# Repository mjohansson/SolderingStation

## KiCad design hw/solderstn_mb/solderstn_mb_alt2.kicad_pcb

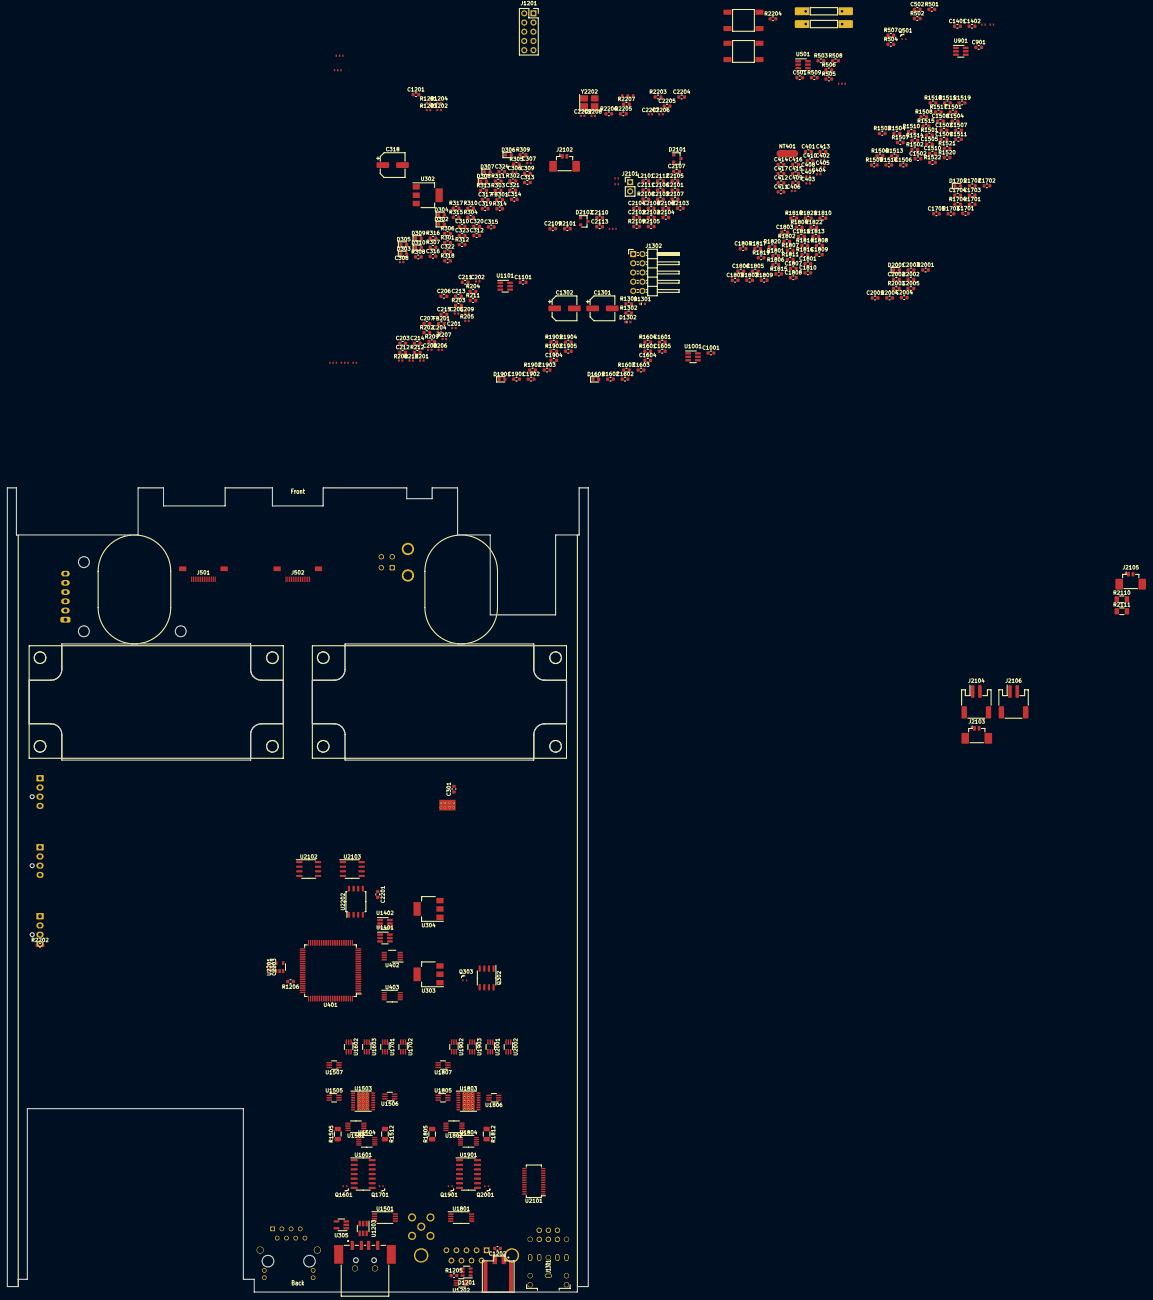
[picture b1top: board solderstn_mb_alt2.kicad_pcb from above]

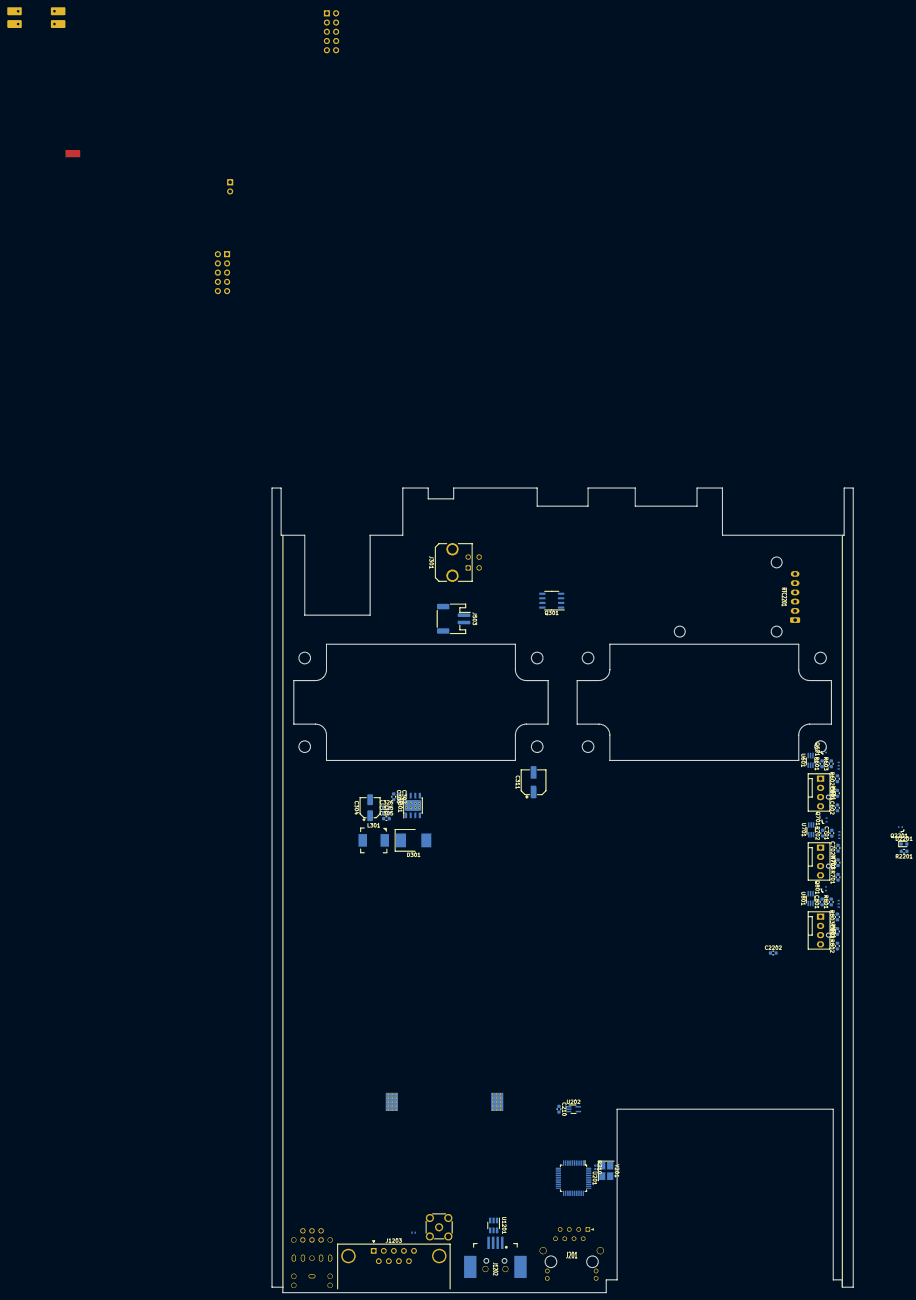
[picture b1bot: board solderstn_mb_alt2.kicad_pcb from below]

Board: 4 copper layers, 160.0 x 221.5 mm, 411 parts (56 on the bottom side), 267 nets, no tracks yet.

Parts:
C201, C202, C204, C205: DNP; C_0402_1005Metric
C203, C206, C207, C210, C211, C213, C215, C301, C309, C317, C321, C411, C416, C417, C501, C502, C602, C702, C802, C901, C1001, C1101, C1201, C1202, C1401, C1402, C1509, C1510, C1511, C1601, C1603, C1604, C1605, C1701, C1703, C1704, C1705, C1809, C1810, C1811, C1901, C1903, C1904, C1905, C2001, C2003, C2004, C2005, C2101, C2107, C2111, C2201, C2202, C2203, C2204, C2205: 100n; C_0603_1608Metric
C208, C209: 27p; C_0402_1005Metric
C212, C214, C302, C303, C305, C312, C313, C319, C320, C322, C323, C324, C325, C326, C401: 10u; C_0603_1608Metric
C304: APXG160ARA101ME61G; CP_Elec_5x5.8
C306: 15n; C_0402_1005Metric
C307: 10pF; C_0402_1005Metric
C308: 3n9; C_0402_1005Metric
C310, C314, C315, C601, C701, C801: 10u/16V; C_0603_1608Metric
C311, C318: UCL1V470MCL1GS; CP_Elec_6.3x5.8
C316, C412, C413, C415, C1508, C1808: 1u; C_0603_1608Metric
C402, C403, C404, C405, C406, C407, C408: 100n; C_0402_1005Metric
C409, C410, C2106, C2109, C2110, C2113: 2u2; C_0603_1608Metric
C414: 22u; C_0603_1608Metric
C1301, C1302: 47u/10V; CP_Elec_6.3x5.8
C1501, C1505, C1507, C1801, C1805, C1807: 10n; C_0603_1608Metric
C1502, C1802: 4n7; C_0603_1608Metric
C1503, C1504, C1506, C1803, C1804, C1806: 220n; C_0603_1608Metric
C1602, C1702, C1902, C2002: 1u/10V; C_0603_1608Metric
C2102: 22n; C_0603_1608Metric
C2103: 4p7; C_0603_1608Metric
C2104, C2108, C2112: 470n; C_0603_1608Metric
C2105: 1n; C_0603_1608Metric
C2206, C2207, C2208, C2209: 10p; C_0402_1005Metric
D301: MBRS340T3G; MBRS3xx_SMC_CASE_403AC
D302: Yellow; LED_0603_1608Metric
D303, D304, D305, D306, D307, D308, D309: Green; LED_0603_1608Metric
D310, D1601, D1701, D1901, D2001: Red; LED_0603_1608Metric
D1201: SP0505BAHT; SOT-23-6
D1301, D1302: SLESD5Z5V; D_SOD-523
D2101, D2102: CM1213A-01SO; SOT-23
D2201: LED_gr; LED_0603_1608Metric
FB201, FB301: 60R@100M; L_0603_1608Metric
J201: 74980104400; 74980104400_WE-RJ45_LAN_trx
J301: Molex_MicroFit_30-43045-0421; Molex_Micro-Fit_3.0_43045-0421_2x02-1MP_P3.00mm_Horizontal
J501, J502: FFC_conn_14p; FPC_14p_05mm-Molex_5052781433
J503: JST_S2B-PH-SM4-TB; JST_PH_S2B-PH-SM4-TB_1x02-1MP_P2.00mm_Horizontal
J1201: Conn_02x05_Odd_Even; PinSocket_2x05_P2.54mm_Vertical
J1202: USB_B-TE_1734346-1; TE_1734346
J1203: DB9_Male_MountingHoles; DSub9-Kycon_K22X-EP9P-N
J1204: USB_A-CUI-UJ2-AH-1-SMT; CUI-UJ2_AH_1_SMT
J1205: Molex_NanoFit-1x02; Molex_NanoFit_105430-1102_1x02_P2.50mm_Horizontal
J1301: SJ-3571N
J1302: Conn_02x05_Odd_Even; PinHeader_2x05_P2.54mm_Horizontal
J2101: Conn_01x02; PinHeader_1x02_P2.54mm_Vertical
J2102: Molex_PicoBlade-53398-0271; Molex_PicoBlade_53398-0271_1x02-1MP_P1.25mm_Vertical
J2103, J2105: CES-30207-158L120-67_Molex-PicoBlade_conn; Molex_PicoBlade_53398-0271_1x02-1MP_P1.25mm_Vertical
J2104, J2106: CES-703116-28PM_JST-conn; JST_PH_S2B-PH-SM4-TB_1x02-1MP_P2.00mm_Horizontal
J2107: Conn_Coaxial; SMA_Molex_73251-2200_Horizontal
JP201, JP1401, JP1402, JP2102, JP2103, JP2106: dogbone_2_ud; db2_ud_0402
JP202, JP203, JP501, JP601, JP701, JP801, JP2101, JP2104, JP2105: dogbone_3_ud; db3_ud_0402
JP2201: dogbone_3_ud; db3_ud_0603
L301: ASPI-0630LR-3R3M-T15; ASPI-0603LR
L2101: 56nH(LQW18AN56NJ00D); L_0603_1608Metric
LS2101, LS2103: CES-30207-158L120-67; CUI_CES-30207
LS2102, LS2104: CES-703116-28PM; CUI_CES-703116-28PM
M501, M502: FFC_retention_clamp; FFC_retention_clamp_14pin_7_5mm
M601, M701, M801: Fan_4pin; FanPinHeader_1x04_P2.54mm_Vertical
NT401: Net-Tie_2; NetTie-2_SMD_Pad2.0mm
Q301, Q302: Si4497DY; SOIC-8_3.9x4.9mm_P1.27mm
Q303, Q501, Q601, Q701, Q801, Q2201: DMG1012T; SOT-523
Q1601, Q1701, Q1901, Q2001: DMG1013T; SOT-523
R201, R205, R206, R207, R208: 5k1; R_0402_1005Metric
R202, R203: 330; R_0603_1608Metric
R204, R211, R212, R302, R304, R307, R308, R309, R502, R509, R602, R603, R702, R703, R802, R803, R1503, R1508, R1509, R1510, R1518, R1519, R1520, R1521, R1522, R1603, R1703, R1803, R1808, R1809, R1810, R1818, R1819, R1820, R1821, R1822, R1903, R2003, R2106, R2109, R2203, R2206: 10k; R_0603_1608Metric
R209, R508, R2207: 0R; R_0603_1608Metric
R210: 0R; R_0402_1005Metric
R213: 6.19k; R_0402_1005Metric
R301: 390k; R_0603_1608Metric
R303: 68k; R_0603_1608Metric
R305: 1k8; R_0603_1608Metric
R306, R312, R313, R314, R1501, R1502, R1504, R1506, R1511, R1514, R1516, R1604, R1704, R1801, R1802, R1804, R1806, R1811, R1814, R1816, R1904, R2004, R2102, R2103, R2201, R2202: 1k; R_0603_1608Metric
R310, R311, R2204, R2205: 4k7; R_0603_1608Metric
R315, R316, R317: 100R; R_0603_1608Metric
R318: 470R; R_0603_1608Metric
R501, R503, R506: 20k; R_0603_1608Metric
R504, R505: 160k; R_0603_1608Metric
R507: 27k; R_0603_1608Metric
R601, R701, R801: 12k; R_0603_1608Metric
R1201, R1202, R1203, R1204: 1k; R_0402_1005Metric
R1205, R1206, R1301, R1302: 100; R_0603_1608Metric
R1505, R1512, R1805, R1812: 10mR; R_1206_3216Metric
R1507, R1517, R1807, R1817: 330k; R_0603_1608Metric
R1513, R1515, R1813, R1815: 5k6; R_0603_1608Metric
R1601, R1602, R1701, R1702, R1901, R1902, R2001, R2002, R2104, R2107: 15k; R_0603_1608Metric
R2101: 560; R_0603_1608Metric
R2105, R2108: 2k2; R_0603_1608Metric
R2110, R2111: 0R; R_1206_3216Metric
RTC2201: DS3231_Module_6pins; DS3231_module_6pin_horizontal_mnt
SW2201, SW2202: Pushbutton_SMD_TS-1102W-4316; SMD_PUSHBTN_6x6mm
U201: IP101GA; LQFP-48_7x7mm_P0.5mm
U202: 74LVC1G126SE; SOT-353_SC-70-5_Handsoldering
U301: TPS54332DDA; TI_SO-PowerPAD-8_ThermalVias
U302, U303, U304: TLV1117LV30DCY; SOT-223-3_TabPin2
U305: AP22811AW5; SOT-23-5_HandSoldering
U401: STM32F429VITx; LQFP-100_14x14mm_P0.5mm
U402: REF6125IDGK; VSSOP-8_3.0x3.0mm_P0.65mm
U403: TLV9052SIDGS; VSSOP-10_3x3mm_P0.5mm
U501: TLV9051SIDBV; SOT-23-6_Handsoldering
U601, U701, U801, U1202: 74LVC2G17gw; SOT-363_SC-70-6_Handsoldering
U901, U1001, U1101: TMP100; SOT-23-6_Handsoldering
U1201, U1203: USBLC6-2SC6; SOT-23-6_Handsoldering
U1401, U1402: TMUX1219; SOT-23-6_Handsoldering
U1501, U1801: AD8552ARU; TSSOP-8_4.4x3mm_P0.65mm
U1502, U1504, U1802, U1804: INA226; VSSOP-10_3x3mm_P0.5mm
U1503, U1803: TPS2HB16AQ1; HTSSOP-16-1EP_4.4x5mm_P0.65mm_EP3.4x5mm_Mask3x3mm_ThermalVi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
U1505, U1506, U1507, U1603, U1702, U1805, U1806, U1807, U1903, U2002: 74LVC1G11dck; SOT-363_SC-70-6_Handsoldering
U1601, U1901: NE556d; SOIC-14_3.9x8.7mm_P1.27mm
U1602, U1701, U1902, U2001: 74LVC1G175dck; SOT-363_SC-70-6_Handsoldering
U2101: Si4735-D60-GU; SSOP-24_3.9x8.7mm_P0.635mm
U2102, U2103: TS4990IDT; SOIC-8_3.9x4.9mm_P1.27mm
U2201: MCP1316T-26LE-OT; SOT-23-5
U2202: W25Q64FV; SOIC-8_5.275x5.275mm_P1.27mm
Y201: TSX-3225 25.0000MF10P-C; Crystal_SMD_SeikoEpson_TSX3225-4Pin_3.2x2.5mm_HandSoldering
Y2202: TSX-3225 16.0000MF18X-AC3; Crystal_SMD_SeikoEpson_TSX3225-4Pin_3.2x2.5mm_HandSoldering

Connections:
+12V: C315.1, C1502.2, C1503.2, C1802.2, C1803.2, Q302.5, Q302.6, Q302.7, Q302.8, R311.1, R1513.1, R1515.2, R1813.1, R1815.2, U1502.8, U1503.17, U1504.8, U1802.8, U1803.17, U1804.8
+VDC: J301.2, J301.3, Q301.5, Q301.6, Q301.7, Q301.8
/Audio & FM-radio/Audio_L_int: J1201.2, R2111.1
/Audio & FM-radio/Audio_R_int: J1201.6, R2110.1
/Audio & FM-radio/FMI: C2105.1, D2102.1, J2102.1, JP2106.1
/Ethernet/50M_CLKO: U201.16, U202.2
/Ethernet/LED0_LINK: J201.11, R208.2, U201.9
/Ethernet/LED1_DUPLEX: R207.2, U201.10
/Ethernet/LED2_10M_LINK_ACT: J201.10, JP201.1, JP201.2, R206.2, U201.12
/Ethernet/LED3_100M_LINK_ACT: R202.2, R205.2, U201.13
/Ethernet/RMII: R211.1, U201.1
/Ethernet/RXN: C205.1, J201.6, U201.30
/Ethernet/RXP: C204.1, J201.3, U201.31
/Ethernet/TXN: C202.1, J201.2, U201.33
/Ethernet/TXP: C201.1, J201.1, U201.34
/Rear panel connections/Audio_L: J1201.1, U2103.8
/Rear panel connections/Audio_R: J1201.5, U2102.8
/Rear panel connections/CH_A_HEATER_1: R1505.1, R1601.1, U1502.10
/Rear panel connections/CH_A_HEATER_2: R1512.1, R1701.1, U1504.10
/Rear panel connections/CH_A_TC1: R1501.2, R1502.2, R1504.1
/Rear panel connections/CH_B_HEATER_1: R1805.1, R1901.1, U1802.10
/Rear panel connections/CH_B_HEATER_2: R1812.1, R2001.1, U1804.10
/Rear panel connections/CH_B_TC1: R1801.2, R1802.2, R1804.1
/Rear panel connections/Headphone connector asm/Audio_L_ch: J1301.8, J1302.1, R1202.2
/Rear panel connections/Headphone connector asm/Audio_R_ch: J1301.5, J1302.5, R1201.2
/Rear panel connections/Headphone connector asm/Audio_int_L: J1301.7, J1302.2, R1203.2
/Rear panel connections/Headphone connector asm/Audio_int_R: J1301.4, J1302.6, R1204.2
/Rear panel connections/Headphone connector asm/L_ch_out: D1301.1, J1301.2, R1302.1
/Rear panel connections/Headphone connector asm/R_ch_out: D1302.1, J1301.3, R1301.1
/STM32F429 MCU/32kHz: JP2201.1, R2202.1, RTC2201.1
/STM32F429 MCU/AUX_HOST_RX: J502.8, U401.97
/STM32F429 MCU/AUX_HOST_TX: J502.9, U401.98
/STM32F429 MCU/CH_A_KTY_REED_BIAS_EN: U401.61, U403.5
/STM32F429 MCU/CH_B_KTY_REED_BIAS_EN: U401.62, U403.6
/STM32F429 MCU/DLED_WDT: Q2201.1, U401.7, U2201.4
/STM32F429 MCU/Flash_MISO: U401.44, U2202.2
/STM32F429 MCU/~Flash_CSn~: U401.41, U2202.1
/STM32F429 MCU/~RTC_INTn~: RTC2201.2, U401.47
/STM32F429 PWR/Vref_2v5: C414.1, C415.1, C416.1, U401.21, U402.5, U402.6, U403.3, U403.7
/Weller contol/CH_A_KTY_REED_BIAS: R1501.1, R1511.1, U403.1, U403.2
/Weller contol/CH_B_KTY_REED_BIAS: R1801.1, R1811.1, U403.8, U403.9
/Weller contol/Channel A/HT1_EN: U1503.4, U1505.4
/Weller contol/Channel A/HT2_EN: U1503.13, U1506.4
/Weller contol/Channel A/PWM error detector 1/~CLR_FLAG~: U1602.6, U1603.4
/Weller contol/Channel A/PWM error detector 1/~PULSE_ERR~: U1601.5, U1603.6
/Weller contol/Channel A/PWM error detector 1/~PULSEn_D~: Q1601.1, R1601.2, R1603.1, U1601.6
/Weller contol/Channel A/PWM error detector 2/~CLR_FLAG~: U1701.6, U1702.4
/Weller contol/Channel A/PWM error detector 2/~PULSE_ERR~: U1601.9, U1702.6
/Weller contol/Channel A/PWM error detector 2/~PULSEn_D~: Q1701.1, R1701.2, R1703.1, U1601.8
/Weller contol/Channel A/PWM_OK_1: D1601.1, U1505.3, U1507.6, U1602.4
/Weller contol/Channel A/PWM_OK_2: D1701.1, U1506.3, U1507.3, U1701.4
/Weller contol/Channel A/Vout1: C1504.2, R1505.2, U1502.9, U1503.6, U1503.7, U1503.8
/Weller contol/Channel A/Vout2: C1506.2, R1512.2, U1503.9, U1503.10, U1503.11, U1504.9
/Weller contol/Channel A/~OC_ERR_1~: R1503.2, U1502.3, U1603.1
/Weller contol/Channel A/~OC_ERR_2~: R1519.2, U1504.3, U1702.1
/Weller contol/Channel B/HT1_EN: U1803.4, U1805.4
/Weller contol/Channel B/HT2_EN: U1803.13, U1806.4
/Weller contol/Channel B/PWM error detector 1/~CLR_FLAG~: U1902.6, U1903.4
/Weller contol/Channel B/PWM error detector 1/~PULSE_ERR~: U1901.5, U1903.6
/Weller contol/Channel B/PWM error detector 1/~PULSEn_D~: Q1901.1, R1901.2, R1903.1, U1901.6
/Weller contol/Channel B/PWM error detector 2/~CLR_FLAG~: U2001.6, U2002.4
/Weller contol/Channel B/PWM error detector 2/~PULSE_ERR~: U1901.9, U2002.6
/Weller contol/Channel B/PWM error detector 2/~PULSEn_D~: Q2001.1, R2001.2, R2003.1, U1901.8
/Weller contol/Channel B/PWM_OK_1: D1901.1, U1805.3, U1807.6, U1902.4
/Weller contol/Channel B/PWM_OK_2: D2001.1, U1806.3, U1807.3, U2001.4
/Weller contol/Channel B/Vout1: C1804.2, R1805.2, U1802.9, U1803.6, U1803.7, U1803.8
/Weller contol/Channel B/Vout2: C1806.2, R1812.2, U1803.9, U1803.10, U1803.11, U1804.9
/Weller contol/Channel B/~OC_ERR_1~: R1803.2, U1802.3, U1903.1
/Weller contol/Channel B/~OC_ERR_2~: R1819.2, U1804.3, U2002.1
/Weller contol/HWID_ADC_SEL: U401.2, U1401.1, U1402.1
AUX_BOOT0: J502.1, U401.1
CH_A_DRV_OK: U401.87, U1507.4
CH_A_FET1_PWM: R1520.1, U401.63, U1505.6
CH_A_FET2_PWM: R1521.1, U401.64, U1506.6
CH_A_IN_STAND_ADC1: R1504.2, U401.15
CH_A_KTY_HWID_MB_ADC2: JP1401.1, JP1401.2, R1511.2, R1514.2, U401.23, U1401.4, U1401.5
CH_A_TC1_AMP_ADC1: R1507.1, U401.17, U1501.1
CH_A_TC2_AMP_ADC2: R1517.1, U401.18, U1501.7
CH_B_DRV_OK: U401.88, U1807.4
CH_B_FET1_PWM: R1820.1, U401.65, U1805.6
CH_B_FET2_PWM: R1821.1, U401.66, U1806.6
CH_B_IN_STAND_ADC1: R1804.2, U401.31
CH_B_KTY_HWID_FP_ADC2: JP1402.1, JP1402.2, R1811.2, R1814.2, U401.26, U1402.4, U1402.5
CH_B_TC1_AMP_ADC1: R1807.1, U401.35, U1801.1
CH_B_TC2_AMP_ADC2: R1817.1, U401.36, U1801.7
DAC_OUT1: C2112.2, U401.29
DAC_OUT2: C2108.2, U401.30
DBGUART_RX: R1206.1, U401.69
DBGUART_TX: U401.68, U1202.1
DISP_D~Cn~: J501.1, U401.38
DISP_FLASH_MOSI: J501.5, U401.45, U2202.5
DISP_FLASH_SCK: J501.4, U401.43, U2202.6
ETH_MDC: U201.25, U401.16
ETH_MDIO: R201.1, U201.26, U401.25
FAN1_PWM: Q601.1, R603.2, U401.90
FAN1_RPM: U401.4, U601.6
FAN2_PWM: Q701.1, R703.2, U401.91
FAN2_RPM: U401.5, U701.6
FAN3_PWM: Q801.1, R803.2, U401.89
FAN3_RPM: U401.96, U801.6
FM_I2S_CK: R2103.1, U401.78
FM_I2S_SD: R2101.1, U401.80
FM_I2S_WS: C2103.2, R2102.1, U401.77
FP_ENC2_A: J501.6, U401.59
FP_ENC2_B: J501.8, U401.60
FP_ENC_A: J502.6, U401.40
FP_ENC_B: J502.4, U401.42
GND: C201.2, C202.2, C203.2, C204.2, C205.2, C206.2, C207.2, C208.1, C209.1, C210.2, C211.2, C212.2, C213.2, C214.2, C215.2, C302.2, C303.2, C304.2, C305.2, C306.2, C307.2, C308.2, C309.2, C310.2, C311.2, C312.2, C313.2, C314.2, C315.2, C316.2, C317.2, C318.2, C319.2, C320.2, C321.2, C322.2, C323.2, C324.2, C325.2, C326.2, C401.2, C402.2, C403.2, C404.2, C405.2, C406.2, C407.2, C408.2, C409.2, C410.2, C501.2, C502.1, C601.1, C602.1, C701.1, C702.1, C801.1, C802.1, C901.2, C1001.2, C1101.2, C1201.1, C1202.1, C1401.2, C1402.2, C1501.2, C1502.1, C1503.1, C1504.1, C1505.2, C1506.1, C1507.1, C1508.1, C1509.1, C1510.1, C1511.1, C1601.2, C1602.2, C1603.2, C1604.2, C1605.2, C1701.2, C1702.2, C1703.2, C1704.2, C1705.2, C1801.2, C1802.1, C1803.1, C1804.1, C1805.2, C1806.1, C1807.1, C1808.1, C1809.1, C1810.1, C1811.1, C1901.2, C1902.2, C1903.2, C1904.2, C1905.2, C2001.2, C2002.2, C2003.2, C2004.2, C2005.2, C2101.2, C2103.1, C2106.1, C2107.1, C2109.1, C2110.1, C2111.1, C2113.1, C2201.1, C2202.1, C2203.2, C2204.1, C2205.1, C2206.2, C2207.2, C2208.1, C2209.1, D301.2, D302.1, D303.1, D304.1, D305.1, D306.1, D307.1, D308.1, D309.1, D1201.2, D1301.2, D1302.2, D2101.2, D2101.3, D2102.2, D2102.3, J301.1, J301.4, J301.MP, J501.3, J501.13, J502.12, J1201.3, J1201.4, J1201.7, J1201.8, J1202.4, J1202.S1, J1202.S2, J1203.0, J1203.5, J1203.6, J1204.4, J1204.S1, J1204.S2, J1205.1, J1205.S1, J1205.S2, J1301.1, J1302.3, J1302.4, J1302.7, J1302.8, J2101.2, J2102.2, J2107.2, JP202.1, JP202.2, JP203.1, JP203.2, JP2101.1, JP2101.2, JP2102.1, JP2102.2, JP2103.1, JP2103.2, L2101.2, M601.1, M701.1, M801.1, NT401.1, Q301.4, Q303.2, Q501.2, Q601.2, Q701.2, Q801.2, Q1601.3, Q1701.3, Q1901.3, Q2001.3, Q2201.2, R203.1, R205.1, R206.1, R207.1, R208.1, R209.2, R212.2, R213.1, R303.2, R305.2, R307.2, R309.2, R507.2, R509.2, R602.1, R603.1, R702.1, R703.1, R802.1, R803.1, R1201.1, R1202.1, R1203.1, R1204.1, R1506.2, R1508.2, R1509.2, R1510.2, R1516.2, R1518.2, R1520.2, R1521.2, R1522.2, R1603.2, R1703.2, R1806.2, R1808.2, R1809.2, R1810.2, R1816.2, R1818.2, R1820.2, R1821.2, R1822.2, R1903.2, R2003.2, R2203.2, R2206.1, RTC2201.6, SW2201.1, SW2201.2, U201.11, U201.17, U201.27, U201.29, U201.35, U201.45, U202.3, U301.4, U301.9, U302.1, U303.1, U304.1, U305.2, U401.10, U401.27, U401.74, U401.99, U501.2, U601.2, U601.3, U701.2, U701.3, U801.2, U801.3, U901.2, U901.3, U1001.2, U1001.5, U1101.2, U1201.2, U1202.2, U1203.2, U1401.3, U1402.3, U1501.4, U1502.1, U1502.2, U1502.7, U1503.1, U1504.1, U1504.7, U1505.2, U1506.2, U1507.2, U1601.7, U1602.2, U1603.2, U1701.2, U1702.2, U1801.4, U1802.2, U1802.7, U1803.1, U1804.7, U1805.2, U1806.2, U1807.2, U1901.7, U1902.2, U1903.2, U2001.2, U2002.2, U2101.9, U2101.13, U2101.14, U2101.16, U2102.7, U2103.7, U2201.2, U2202.4, Y201.2, Y201.4, Y2202.2, Y2202.4
GNDA: C411.2, C412.2, C413.1, C414.2, C415.2, C416.2, C417.2, NT401.2, U401.20, U402.7, U402.8
GNDPWR: J201.8, J201.13, J201.14, R209.1
HWID_FP: J502.11, U1402.6
HWID_MB: U501.1, U501.4, U1401.6
I2C1_SCL: J501.9, R2204.1, RTC2201.3, U401.92, U901.1, U1001.1, U1101.1, U1502.5, U1504.5, U1802.5, U1804.5, U2101.17
I2C1_SDA: J501.7, R2205.1, RTC2201.4, U401.93, U901.6, U1001.6, U1101.6, U1502.4, U1504.4, U1802.4, U1804.4, U2101.18
MCU_BOOT0: C2204.2, D1201.5, J1203.4, R2206.2, SW2202.1, SW2202.2, U401.94
unnamed: C206.1, J201.4
unnamed: C207.1, J201.5
unnamed: C208.2, R210.1, Y201.1
unnamed: C209.2, U201.46, Y201.3
unnamed: C212.1, C213.1, FB201.1, U201.36
unnamed: C214.1, C215.1, U201.8
unnamed: C301.1, D301.1, L301.1, U301.3
unnamed: C301.2, U301.1
unnamed: C306.1, U301.8
unnamed: C307.1, R304.1, U301.6
unnamed: C308.1, R304.2
unnamed: C320.1, C321.1, FB301.2, U303.2
unnamed: C409.1, U401.73
unnamed: C410.1, U401.49
unnamed: C413.2, U402.4
unnamed: C502.2, R502.2, R503.2, R504.2, R505.2, R506.2, R507.1, U501.3
unnamed: C1301.1, J1301.6
unnamed: C1301.2, R1301.2
unnamed: C1302.1, J1301.9
unnamed: C1302.2, R1302.2
unnamed: C1601.1, U1601.3
unnamed: C1602.1, Q1601.2, R1602.2, U1601.1, U1601.2
unnamed: C1701.1, U1601.11
unnamed: C1702.1, Q1701.2, R1702.2, U1601.12, U1601.13
unnamed: C1901.1, U1901.3
unnamed: C1902.1, Q1901.2, R1902.2, U1901.1, U1901.2
unnamed: C2001.1, U1901.11
unnamed: C2002.1, Q2001.2, R2002.2, U1901.12, U1901.13
unnamed: C2102.2, U2101.22
unnamed: C2104.1, D2101.1, J2101.1
unnamed: C2104.2, U2101.12
unnamed: C2105.2, L2101.1, U2101.8
unnamed: C2108.1, R2106.2
unnamed: C2109.2, U2102.2, U2102.3
unnamed: C2112.1, R2109.2
unnamed: C2113.2, U2103.2, U2103.3
unnamed: C2206.1, U401.12, Y2202.1
unnamed: C2207.1, R2207.1, Y2202.3
unnamed: C2208.2, JP2201.2, U401.8
unnamed: C2209.2, JP2201.3, U401.9
unnamed: D302.2, R310.2
unnamed: D303.2, R311.2
unnamed: D304.2, R312.2
unnamed: D305.2, R313.2
unnamed: D306.2, R314.2
unnamed: D307.2, R315.2
unnamed: D308.2, R316.2
unnamed: D309.2, R317.2
unnamed: D310.2, R318.2
unnamed: D1201.1, J1203.2, U1202.3
unnamed: D1201.6, J1203.3, R1205.2
unnamed: D1601.2, R1604.2
unnamed: D1701.2, R1704.2
unnamed: D1901.2, R1904.2
unnamed: D2001.2, R2004.2
unnamed: D2201.1, Q2201.3
unnamed: D2201.2, R2201.1
unnamed: J201.9, R202.1
unnamed: J201.12, R203.2
unnamed: J503.1, R508.2
unnamed: J503.2, Q501.3
unnamed: J1202.2, U1201.6
unnamed: J1202.3, U1201.4
unnamed: J1204.2, U1203.4
unnamed: J1204.3, U1203.6
unnamed: J2103.1, J2104.1, R2110.2
unnamed: J2103.2, J2104.2, R2105.1, U2102.5
unnamed: J2105.1, J2106.1, R2111.2
unnamed: J2105.2, J2106.2, R2108.1, U2103.5
unnamed: J2107.1, JP2106.2
unnamed: M601.3, R601.1, R602.2, U601.1
unnamed: M601.4, Q601.3
unnamed: M701.3, R701.1, R702.2, U701.1
unnamed: M701.4, Q701.3
unnamed: M801.3, R801.1, R802.2, U801.1
unnamed: M801.4, Q801.3
unnamed: Q302.4, Q303.3, R306.2
unnamed: R210.2, U201.47
unnamed: R212.1, U201.23
unnamed: R213.2, U201.28
unnamed: R301.2, R303.1, U301.7
unnamed: R302.2, R305.1, U301.5
unnamed: R501.2, R506.1
unnamed: R1205.1, U1202.6
unnamed: R1206.2, U1202.4
unnamed: R1502.1, U1501.3
unnamed: R1506.1, R1507.2, U1501.2
unnamed: R1508.1, U1503.16
unnamed: R1509.1, U1503.14
unnamed: R1510.1, U1503.15
unnamed: R1513.2, U1503.5
unnamed: R1514.1, U1501.5
unnamed: R1515.1, U1503.12
unnamed: R1516.1, R1517.2, U1501.6
unnamed: R1518.1, U1503.2
unnamed: R1802.1, U1801.3
unnamed: R1806.1, R1807.2, U1801.2
unnamed: R1808.1, U1803.16
unnamed: R1809.1, U1803.14
unnamed: R1810.1, U1803.15
unnamed: R1813.2, U1803.5
unnamed: R1814.1, U1801.5
unnamed: R1815.1, U1803.12
unnamed: R1816.1, R1817.2, U1801.6
unnamed: R1818.1, U1803.2
unnamed: R2101.2, U2101.1
unnamed: R2102.2, U2101.2
unnamed: R2103.2, U2101.3
unnamed: R2104.1, R2105.2
unnamed: R2104.2, R2106.1, U2102.4
unnamed: R2107.1, R2108.2
unnamed: R2107.2, R2109.1, U2103.4
unnamed: R2207.2, U401.13
PWRBTN_LED_PWM: Q501.1, R509.1, U401.95
PWRDRV_ENABLE: Q303.1, R307.1, R1522.1, R1822.1, U401.58, U1503.3, U1505.1, U1506.1, U1602.1, U1701.1, U1803.3, U1805.1, U1806.1, U1902.1, U2001.1
RCLKo_8M: U401.67, U2101.19
RMII_CRS_DV: U201.22, U401.32
RMII_REF_CLK: U201.7, U202.4, U401.24
RMII_RX_D0: U201.21, U401.33
RMII_RX_D1: U201.20, U401.34
RMII_TX_D0: U201.6, U401.51
RMII_TX_D1: U201.5, U401.52
RMII_TX_EN: U201.2, U401.48
SWCLK: D1201.4, J1203.8, U401.76
SWDIO: D1201.3, J1203.7, U401.72
USB1_DM: U401.70, U1201.1
USB1_DP: U401.71, U1201.3
USB2_DM: U401.53, U1203.3
USB2_DP: U401.54, U1203.1
VBUS: J1202.1, R313.1, U1201.5
VBUS2_ENABLE: R309.1, U305.4, U401.57
VBUS_2: C317.1, C318.1, J1204.1, R314.1, U305.1, U1203.5
VCC: C210.1, C211.1, C324.1, C401.1, C402.1, C403.1, C404.1, C405.1, C406.1, C407.1, C408.1, C501.1, C602.2, C702.2, C802.2, C901.1, C1001.1, C1101.1, C1201.2, C1401.1, C1402.1, C1501.1, C1505.1, C1509.2, C1510.2, C1511.2, C1604.1, C1605.1, C1704.1, C1705.1, C1801.1, C1805.1, C1809.2, C1810.2, C1811.2, C1904.1, C1905.1, C2004.1, C2005.1, C2101.1, C2201.2, C2202.2, C2203.1, FB201.2, J1203.9, JP202.3, JP203.3, JP2101.3, JP2104.3, JP2105.3, R201.2, R204.1, R211.2, R308.2, R315.1, R318.1, R501.1, R502.1, R503.1, R504.1, R505.1, R1503.1, R1519.1, R1604.1, R1704.1, R1803.1, R1819.1, R1904.1, R2004.1, R2201.2, R2202.2, R2204.2, R2205.2, RTC2201.5, SW2202.3, SW2202.4, U201.14, U202.1, U202.5, U304.2, U401.6, U401.11, U401.19, U401.28, U401.50, U401.75, U401.100, U501.5, U501.6, U601.5, U701.5, U801.5, U901.4, U1001.4, U1101.4, U1101.5, U1202.5, U1401.2, U1402.2, U1502.6, U1504.2, U1504.6, U1505.5, U1506.5, U1507.1, U1507.5, U1602.3, U1602.5, U1603.5, U1701.3, U1701.5, U1702.5, U1802.1, U1802.6, U1804.1, U1804.2, U1804.6, U1805.5, U1806.5, U1807.1, U1807.5, U1902.3, U1902.5, U1903.5, U2001.3, U2001.5, U2002.5, U2101.20, U2201.5, U2202.3, U2202.7, U2202.8
VDDA: C322.1, C411.1, C412.1, C417.1, C1507.2, C1508.2, C1807.2, C1808.2, C2102.1, FB301.1, R317.1, U401.22, U402.1, U402.2, U402.3, U1501.8, U1801.8, U2101.21
VDD_OLED: C313.1, J501.2, J502.7, J502.10, R316.1, U302.2
VIN: C302.1, C303.1, C309.1, C310.1, C311.1, C314.1, C1202.2, J1205.2, JP501.3, JP601.3, JP701.3, JP801.3, Q301.1, Q301.2, Q301.3, Q302.1, Q302.2, Q302.3, R301.1, R306.1, R310.1, U301.2
VMAIN: C304.1, C305.1, C312.1, C316.1, C319.1, C323.1, C325.1, C326.1, C601.2, C701.2, C801.2, C1603.1, C1703.1, C1903.1, C2003.1, C2106.2, C2107.2, C2110.2, C2111.2, JP501.1, JP501.2, JP601.1, JP601.2, JP701.1, JP701.2, JP801.1, JP801.2, JP2104.1, JP2104.2, JP2105.1, JP2105.2, L301.2, M601.2, M701.2, M801.2, R302.1, R312.1, R508.1, R601.2, R701.2, R801.2, R1602.1, R1702.1, R1902.1, R2002.1, U302.3, U303.3, U304.3, U305.5, U1601.4, U1601.10, U1601.14, U1901.4, U1901.10, U1901.14, U2102.6, U2103.6
~AUDIO_MUTEn~: U401.3, U2102.1, U2103.1
~AUX_INTn~: J502.3, U401.55
~DISP_CSn~: J501.11, U401.39
~EXT_RSTn~: J1203.1, SW2201.3, SW2201.4, U2201.3
~FM_INTn~: U401.79, U2101.4
~FP_BTN_1An~: J501.14, U401.81
~FP_BTN_1Bn~: J501.12, U401.82
~FP_BTN_2An~: J502.14, U401.83
~FP_BTN_2Bn~: J502.13, U401.84
~FP_ENC2_SWn~: J501.10, U401.86
~FP_ENC_SWn~: J502.2, U401.85
~MCU_RSTn~: C2205.2, U401.14, U1603.3, U1702.3, U1903.3, U2002.3, U2201.1
~PHY_IRQn~: R204.2, U201.48, U401.46
~SYS_RSTn~: C203.1, J502.5, R2203.1, U201.42, U401.37, U2101.15
~VBUS2_FLGn~: D310.1, R308.1, U305.3, U401.56

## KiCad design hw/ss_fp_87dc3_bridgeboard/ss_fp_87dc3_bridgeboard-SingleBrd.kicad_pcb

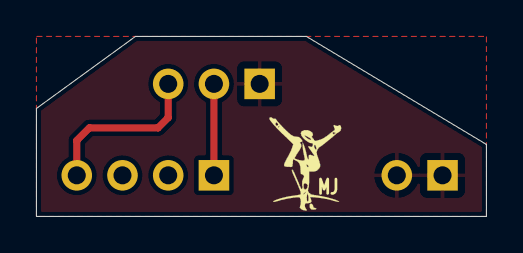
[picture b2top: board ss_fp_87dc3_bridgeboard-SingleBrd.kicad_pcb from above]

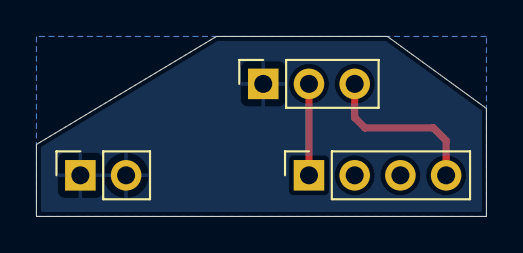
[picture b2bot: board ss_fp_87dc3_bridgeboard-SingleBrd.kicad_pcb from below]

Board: 2 copper layers, 25.0 x 10.0 mm, 4 parts (3 on the bottom side), 3 nets.

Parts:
J104: Conn_01x02; PinSocket_1x02_P2.54mm_Vertical
J105: Conn_01x04; PinSocket_1x04_P2.54mm_Vertical
J106: Conn_01x03; PinSocket_1x03_P2.54mm_Vertical
Logo102: Logo_MJ; MJ_Mini

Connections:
/COM_2: J104.1, J104.2, J106.1
unnamed: J105.1, J106.2
unnamed: J105.4, J106.3

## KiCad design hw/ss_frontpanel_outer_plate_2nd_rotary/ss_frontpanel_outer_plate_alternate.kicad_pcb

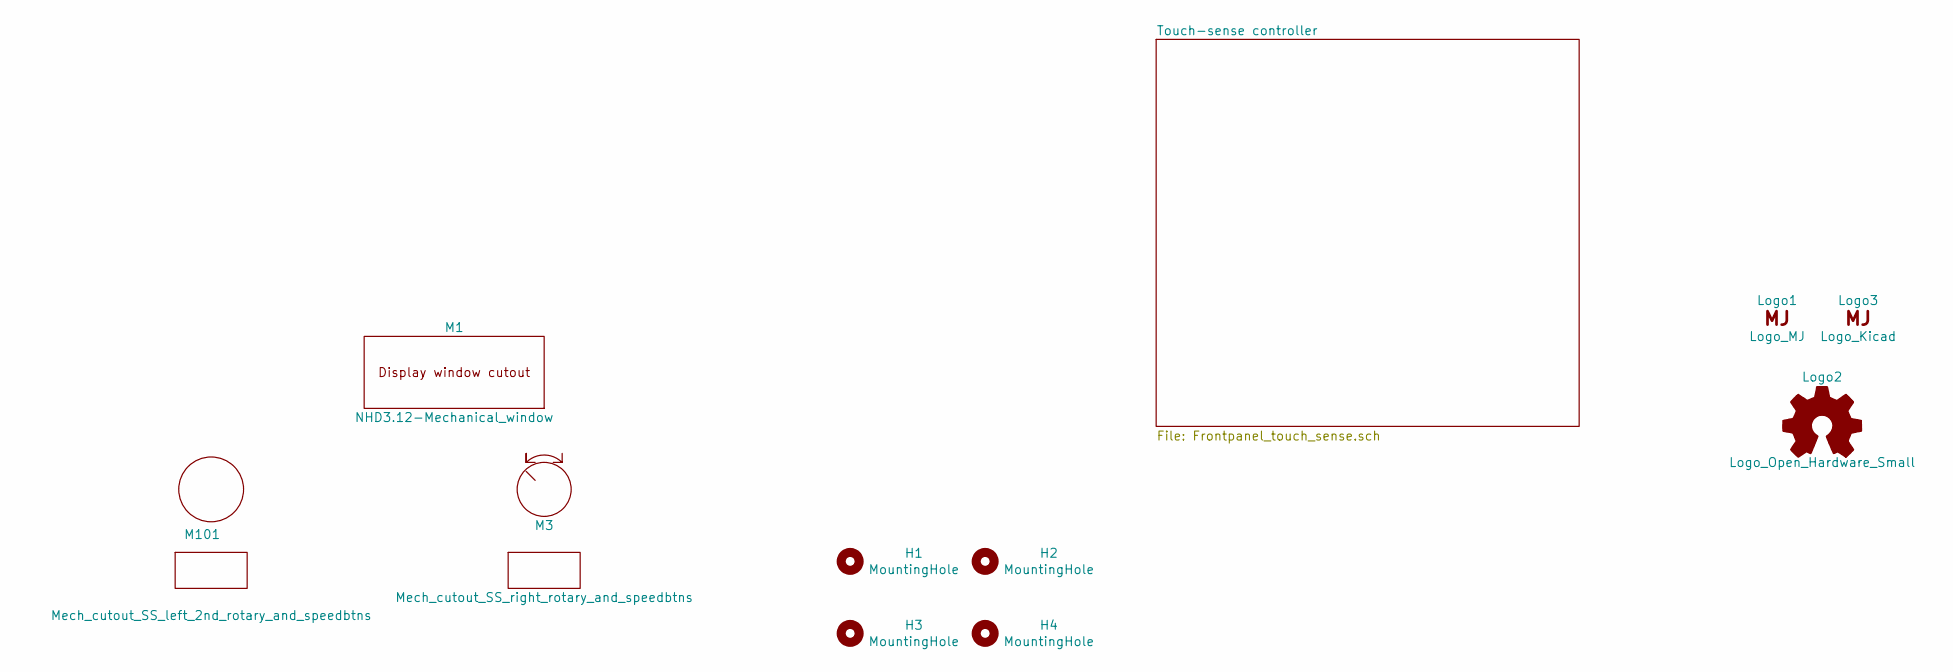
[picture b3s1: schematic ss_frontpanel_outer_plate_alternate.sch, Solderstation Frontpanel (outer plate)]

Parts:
H1, H2, H3, H4: MountingHole; MountingHole_3.5mm_Hammond_panel_screws
Logo1: Logo_MJ; MJ_10.3x12.7
Logo2: Logo_Open_Hardware_Small; OSHW-Logo_5.7x6mm_SilkScreen
Logo3: Logo_Kicad; KiCad-Logo2_5mm_SilkScreen
M1: NHD3.12-Mechanical_window; NHD3_12-Reverse_Bezel
M3: Mech_cutout_SS_right_rotary_and_speedbtns; Frontpanel_R_RotaryEnc_Pushbtns_outer_cutouts
M101: Mech_cutout_SS_left_2nd_rotary_and_speedbtns; Frontpanel_L_Hybrid_Rotary_Pushbtns_outer_cutouts

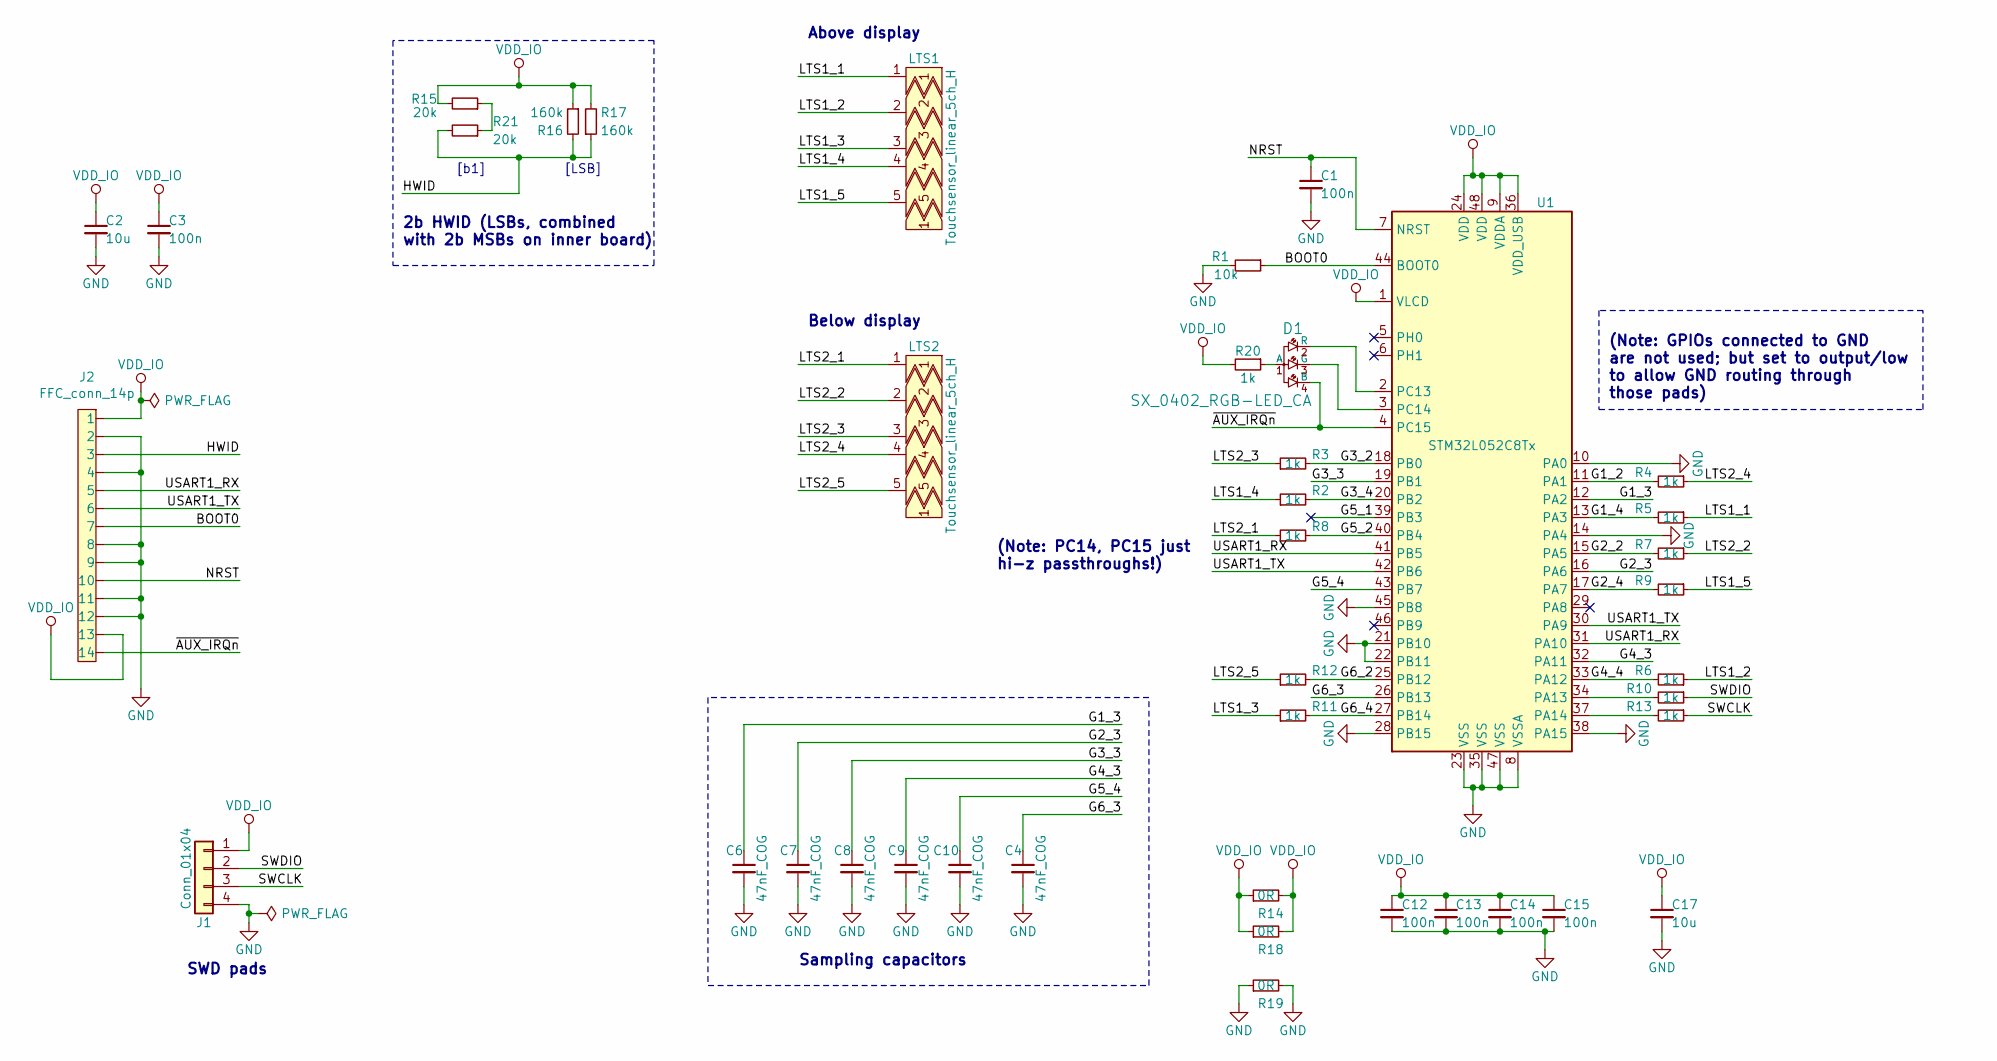
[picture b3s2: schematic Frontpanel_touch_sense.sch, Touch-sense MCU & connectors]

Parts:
C1, C3, C12, C13, C14, C15: 100n; C_0402_1005Metric
C2, C17: 10u; C_0402_1005Metric
C4, C6, C7, C8, C9, C10: 47nF_COG; C_1206_3216Metric
D1: SX_0402_RGB-LED_CA; SX_0402_RGB-CA-06
J1: Conn_01x04; 4pin_SWD_SMT_100mil
J2: FFC_conn_14p; FPC_14p_05mm-WE_687114182122
LTS1, LTS2: Touchsensor_linear_5ch_H; Touchsensor_linear_slider-5ch_H_90x8mm
R1: 10k; R_0402_1005Metric
R2, R3, R4, R5, R6, R7, R9, R10, R13, R20: 1k; R_0402_1005Metric
R8, R11: 1k; R_0603_1608Metric
R12: 1k; R_1206_3216Metric
R14, R18, R19: 0R; R_0603_1608Metric
R15, R21: 20k; R_0402_1005Metric
R16, R17: 160k; R_0402_1005Metric
U1: STM32L052C8Tx; LQFP-48_7x7mm_P0.5mm

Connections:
/Touch-sense controller/BOOT0: J2.7, R1.1, U1.44 (BOOT0)
/Touch-sense controller/G1_2: R4.2, U1.11 (PA1)
/Touch-sense controller/G1_3: C6.1, U1.12 (PA2)
/Touch-sense controller/G1_4: R5.2, U1.13 (PA3)
/Touch-sense controller/G2_2: R7.2, U1.15 (PA5)
/Touch-sense controller/G2_3: C7.1, U1.16 (PA6)
/Touch-sense controller/G2_4: R9.2, U1.17 (PA7)
/Touch-sense controller/G3_2: R3.2, U1.18 (PB0)
/Touch-sense controller/G3_3: C8.1, U1.19 (PB1)
/Touch-sense controller/G3_4: R2.2, U1.20 (PB2)
/Touch-sense controller/G4_3: C9.1, U1.32 (PA11)
/Touch-sense controller/G4_4: R6.2, U1.33 (PA12)
/Touch-sense controller/G5_1: U1.39 (PB3)
/Touch-sense controller/G5_2: R8.2, U1.40 (PB4)
/Touch-sense controller/G5_4: C10.1, U1.43 (PB7)
/Touch-sense controller/G6_2: R12.2, U1.25 (PB12)
/Touch-sense controller/G6_3: C4.1, U1.26 (PB13)
/Touch-sense controller/G6_4: R11.2, U1.27 (PB14)
/Touch-sense controller/HWID: J2.3, R16.2, R17.1, R21.2
/Touch-sense controller/LTS1_1: LTS1.1, R5.1
/Touch-sense controller/LTS1_2: LTS1.2, R6.1
/Touch-sense controller/LTS1_3: LTS1.3, R11.1
/Touch-sense controller/LTS1_4: LTS1.4, R2.1
/Touch-sense controller/LTS1_5: LTS1.5, R9.1
/Touch-sense controller/LTS2_1: LTS2.1, R8.1
/Touch-sense controller/LTS2_2: LTS2.2, R7.1
/Touch-sense controller/LTS2_3: LTS2.3, R3.1
/Touch-sense controller/LTS2_4: LTS2.4, R4.1
/Touch-sense controller/LTS2_5: LTS2.5, R12.1
/Touch-sense controller/NRST: C1.1, J2.10, U1.7 (NRST)
/Touch-sense controller/SWCLK: J1.3, R13.1
/Touch-sense controller/SWDIO: J1.2, R10.1
/Touch-sense controller/USART1_RX: J2.5, U1.31 (PA10), U1.41 (PB5)
/Touch-sense controller/USART1_TX: J2.6, U1.30 (PA9), U1.42 (PB6)
/Touch-sense controller/~AUX_IRQn~: D1.4 (B), J2.14, U1.4 (PC15)
GND: C1.2, C2.2, C3.2, C4.2, C6.2, C7.2, C8.2, C9.2, C10.2, C12.2, C13.2, C14.2, C15.2, C17.2, J1.4, J2.2, J2.4, J2.8, J2.9, J2.11, J2.12, R1.2, R19.1, R19.2, U1.8 (VSSA), U1.10 (PA0), U1.14 (PA4), U1.21 (PB10), U1.22 (PB11), U1.23 (VSS), U1.28 (PB15), U1.35 (VSS), U1.38 (PA15), U1.45 (PB8), U1.47 (VSS)
unnamed: D1.1 (A), R20.1
unnamed: D1.2 (R), U1.2 (PC13)
unnamed: D1.3 (G), U1.3 (PC14)
unnamed: R10.2, U1.34 (PA13)
unnamed: R13.2, U1.37 (PA14)
unnamed: R15.1, R21.1
VDD_IO: C2.1, C3.1, C12.1, C13.1, C14.1, C15.1, C17.1, J1.1, J2.1, J2.13, R14.1, R14.2, R15.2, R16.1, R17.2, R18.1, R18.2, R20.2, U1.1 (VLCD), U1.9 (VDDA), U1.24 (VDD), U1.36 (VDD_USB), U1.48 (VDD)

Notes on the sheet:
Sampling capacitors
Above display
Below display
2b HWID (LSBs, combined with 2b MSBs on inner board)
SWD pads
(Note: PC14, PC15 just hi-z passthroughs!)
(Note: GPIOs connected to GND are not used; but set to output/low to allow GND routing through those pads)
[LSB]
[b1]
